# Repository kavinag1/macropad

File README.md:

# Hackpad Project Submission

This repository contains the full source and production package for a Seeed XIAO RP2040 macropad.

## 1. Create and connect a GitHub repository

If you have not already created a remote repo, use this flow:

```bash
git init
git add .
git commit -m "Initial hackpad submission package"
git branch -M main
git remote add origin https://github.com/<your-username>/<your-repo>.git
git push -u origin main
```

If you already created a repo on GitHub first, clone it and copy these project files into that clone, then run:

```bash
git add .
git commit -m "Add hackpad design, firmware, and production files"
git push
```

## 2. Project structure

Top-level folders in this project:

- CAD
- PCB
- Firmware
- production
- gallery

### CAD

Single assembled case/model source file:

- CAD/full_macropad.step

### PCB

KiCad source files:

- PCB/schem.kicad_pro
- PCB/schem.kicad_sch
- PCB/schem.kicad_pcb

### Firmware

Firmware source files:

- Firmware/qmk/xiao_macropad (QMK port only)

### production

Manufacturing/build outputs:

- production/gerbers.zip
- production/Top.step
- production/Bottom.step
- production/knurled_knob v12.step
- production/firmware.uf2

## 3. Production file checklist

1. PCB Gerbers: Present as production/gerbers.zip
2. Case part exports: Present as STEP files in production/
3. Firmware binary: Place the compiled UF2 at production/firmware.uf2

QMK compile command (from qmk_firmware):

```bash
qmk compile -kb xiao_macropad -km default
```

After compile, copy the generated UF2 into production/ and rename it to firmware.uf2.

## 4. QMK coding keymap (default)

This keymap is intentionally set up for coding workflows:

- Key 1 (SW1): Ctrl+S (Save)
- Key 2 (SW2): Ctrl+F (Find)
- Key 3 (SW3): Ctrl+/ (Toggle comment)
- Key 4 (SW4): Ctrl+Z (Undo)
- Encoder press (SW5): Ctrl+Shift+B (Build task)
- Encoder clockwise: Ctrl+PgDn (Next tab)
- Encoder counter-clockwise: Ctrl+PgUp (Previous tab)

## 5. Required screenshots

README embeds:

### Overall Hackpad

### Schematic

### PCB

### Case Assembly

## 6. BOM

| Item | Qty | Notes |
|---|---:|---|
| Seeed XIAO RP2040 (through-hole) | 1 | Main MCU |
| MX-compatible mechanical switch | 4 | SW1-SW4 |
| EC11 rotary encoder with push switch | 1 | SW5 |
| SSD1306 0.91 inch 128x32 I2C OLED | 1 | Display module |
| Keycaps | 4 | For switch keys |
| Encoder knob | 1 | Rotary control |
| PCB | 1 | 2-layer design |
| 3D printed case parts | 2+ | Top and bottom (plus any extra parts) |

## 7. Design requirements quick check

- MCU: Seeed XIAO RP2040 through-hole footprint used
- PCB source present and intended as 2-layer design
- Input count: 5 total inputs (4 keys + 1 encoder press) plus encoder rotation
- Case and PCB source/manufacturing files included

If you want, I can also generate a small pre-flight script that checks these required files automatically before you submit.

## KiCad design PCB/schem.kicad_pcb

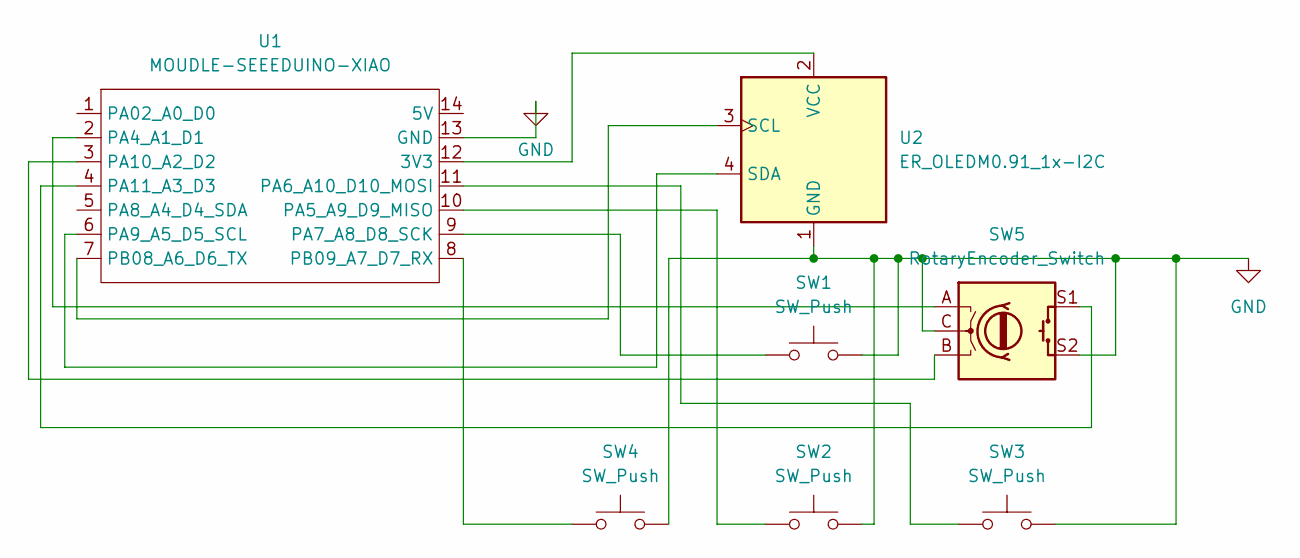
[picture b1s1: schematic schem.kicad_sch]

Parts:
SW1, SW2, SW3, SW4: SW_Push; SW_Cherry_MX_1.00u_PCB
SW5: RotaryEncoder_Switch; RotaryEncoder_Alps_EC11E-Switch_Vertical_H20mm
U1: MOUDLE-SEEEDUINO-XIAO; XIAO-Generic-Hybrid-14P-2.54-21X17.8MM
U2: ER_OLEDM0.91_1x-I2C

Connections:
GND: SW1.2, SW2.2, SW3.2, SW4.2, SW5.C, SW5.S2, U1.13 (GND), U2.1 (GND)
unnamed: U1.12 (3V3), U2.2 (VCC)
unnamed: SW5.A, U1.2 (PA4_A1_D1)
unnamed: SW2.1, U1.10 (PA5_A9_D9_MISO)
unnamed: SW3.1, U1.11 (PA6_A10_D10_MOSI)
unnamed: SW1.1, U1.9 (PA7_A8_D8_SCK)
unnamed: U1.6 (PA9_A5_D5_SCL), U2.4 (SDA)
unnamed: SW5.B, U1.3 (PA10_A2_D2)
unnamed: SW5.S1, U1.4 (PA11_A3_D3)
unnamed: U1.7 (PB08_A6_D6_TX), U2.3 (SCL)
unnamed: SW4.1, U1.8 (PB09_A7_D7_RX)

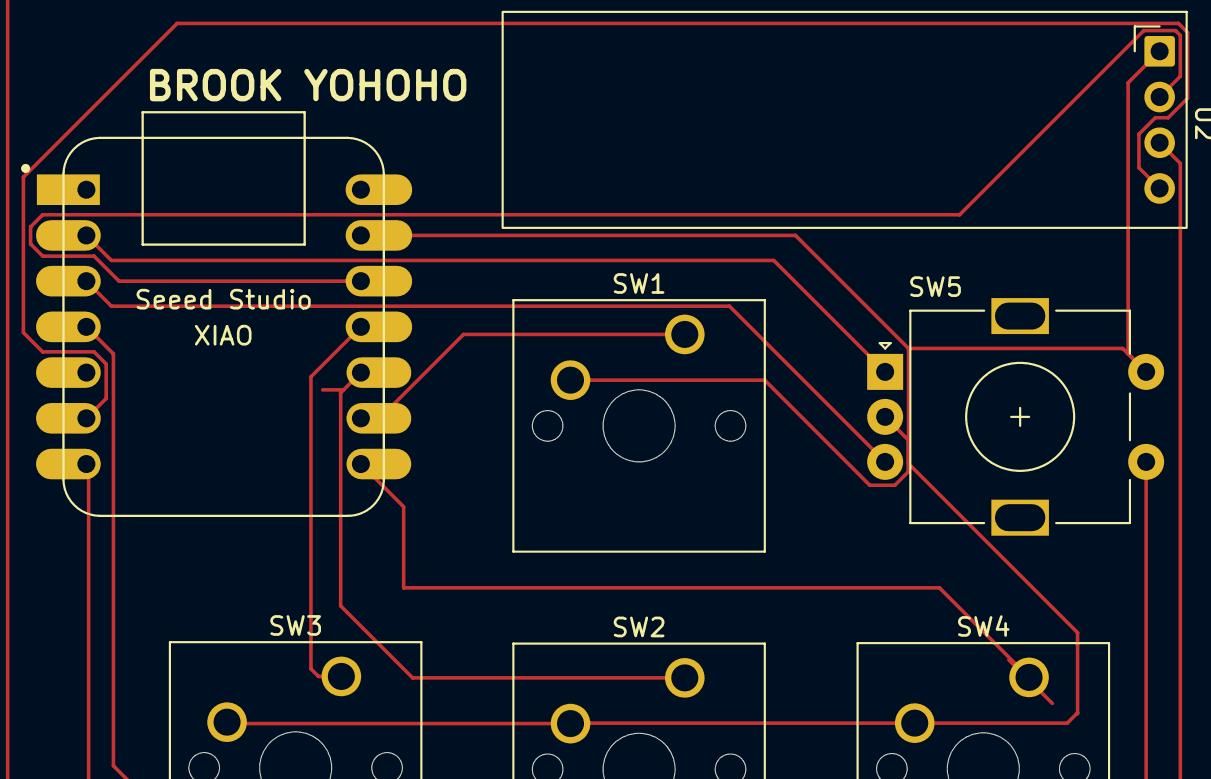
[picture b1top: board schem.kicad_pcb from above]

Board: 2 copper layers, 7 parts (0 on the bottom side), 11 nets.

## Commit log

2026-03-24 Finalize hackpad package with QMK-only firmware and screenshots
